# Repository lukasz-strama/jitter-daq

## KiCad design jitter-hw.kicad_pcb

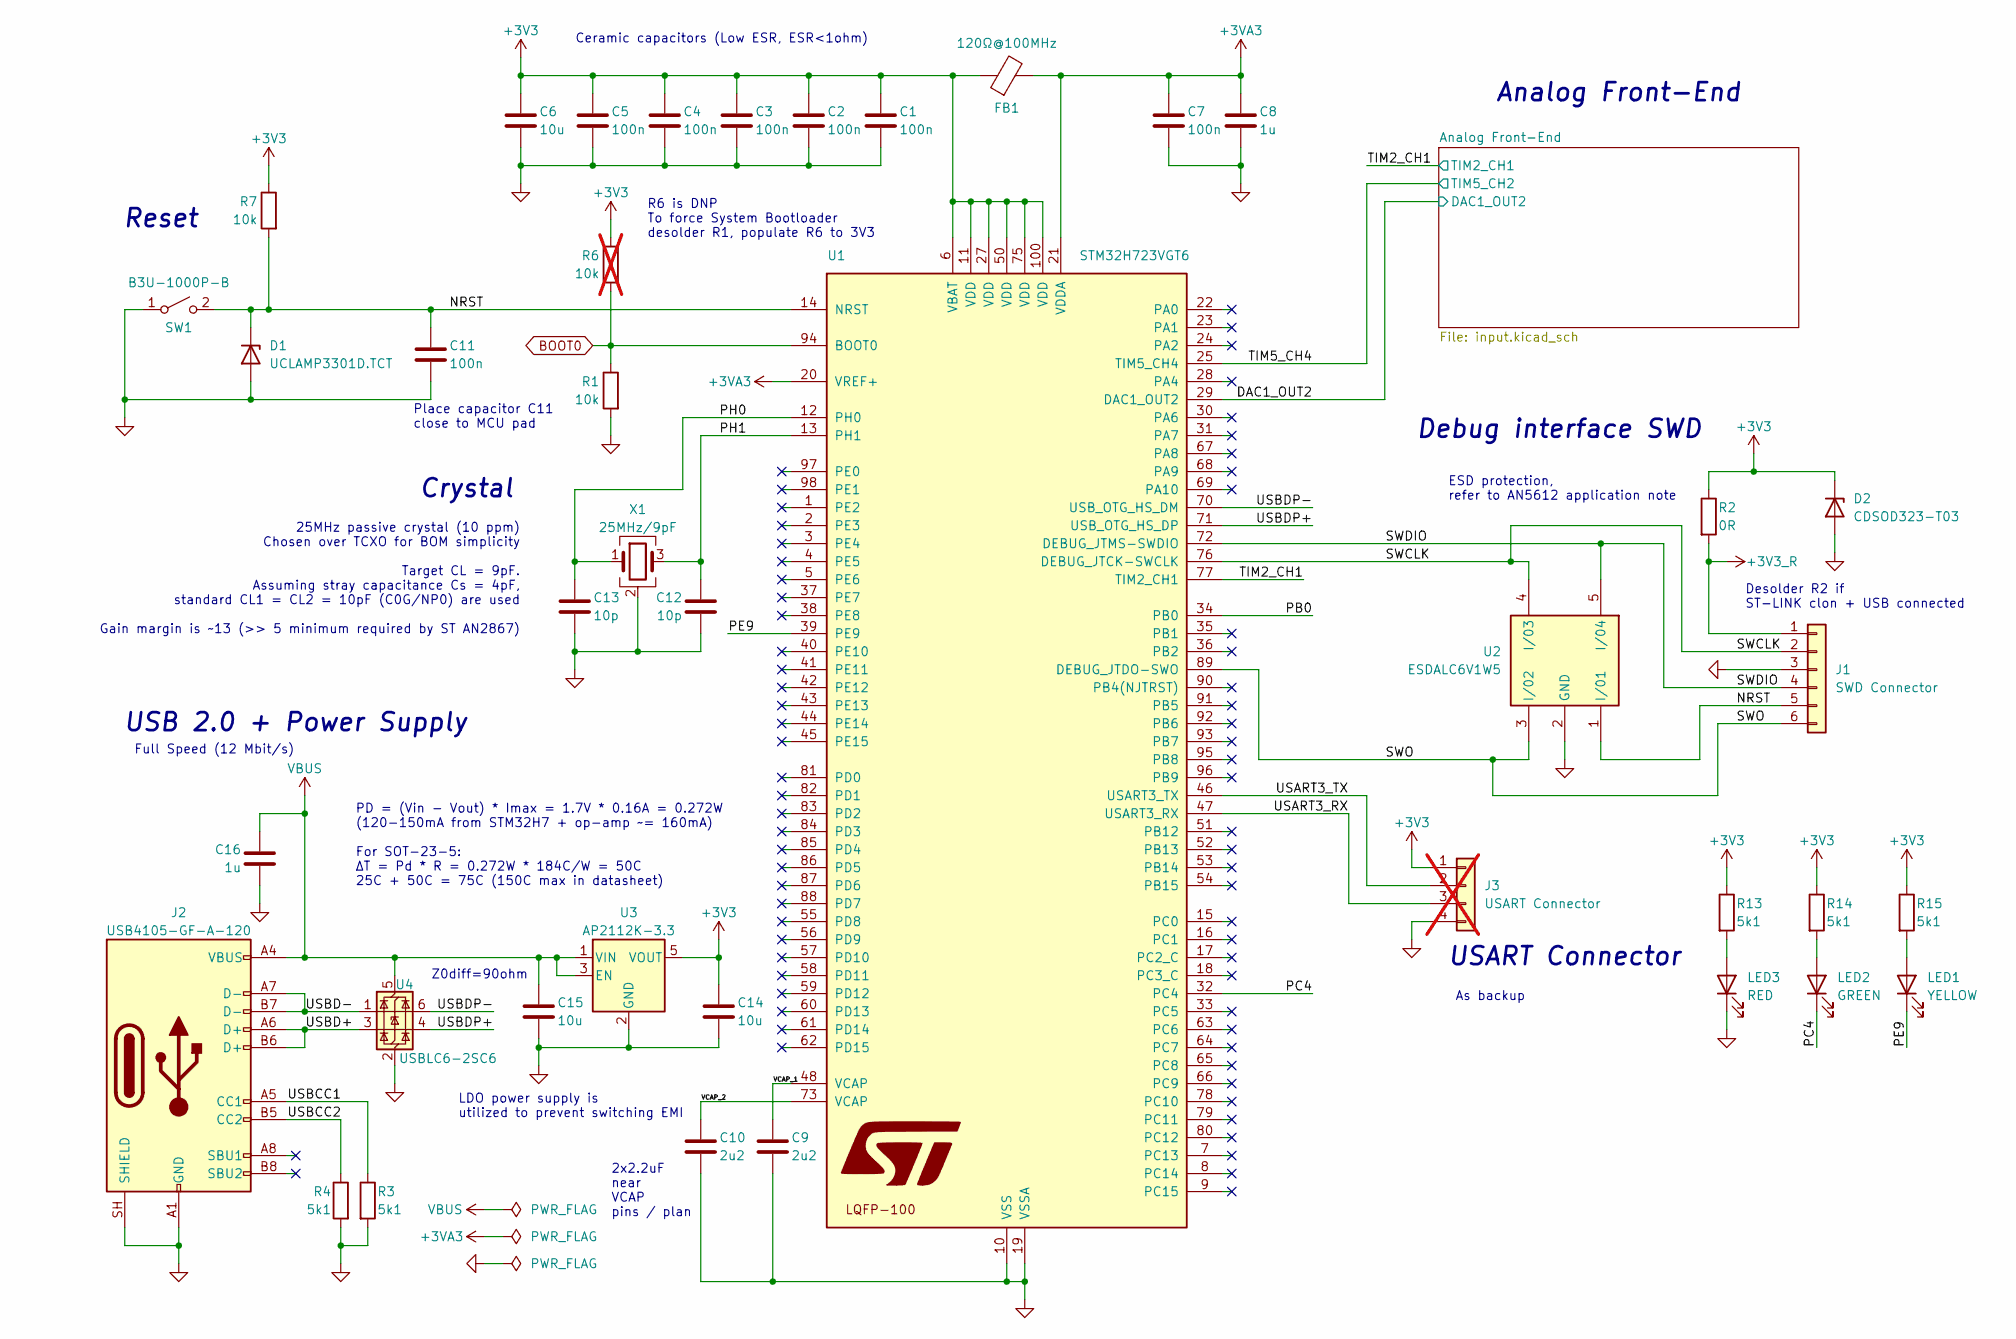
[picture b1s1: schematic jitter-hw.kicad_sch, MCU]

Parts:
C1, C2, C3, C4, C5, C7, C11: 100n; C_0603_1608Metric; Voltage 50V; Tolerance ±10%; MPN CL10B104KB8NNNC; DigiKey Part Number 1276-1000-1-ND
C6, C14, C15: 10u; C_0805_2012Metric; Voltage 25V; Tolerance ±10%; MPN CL21A106KAYNNNG; DigiKey Part Number 1276-6454-1-ND
C8, C16: 1u; C_0603_1608Metric; Voltage 25V; Tolerance ±10%; MPN CL10A105KA8NNNC; DigiKey Part Number 1276-1102-1-ND
C9, C10: 2u2; C_0603_1608Metric; Voltage 10V; Tolerance ±10%; MPN CL10B225KP8NNNC; DigiKey Part Number 1276-1134-1-ND
C12, C13: 10p; C_0603_1608Metric; Voltage 50V; Tolerance ±5%; MPN CL10C100JB8NNNC; DigiKey Part Number 1276-1027-1-ND
D1: UCLAMP3301D.TCT; D_SOD-323_HandSoldering; Voltage - Breakdown 3.5V; Voltage - Clamping 9.5V; MPN UCLAMP3301D.TCT; DigiKey Part Number UCLAMP3301DCT-ND
D2: CDSOD323-T03; D_SOD-323_HandSoldering; MPN CDSOD323-T03
FB1: 120Ω@100MHz; L_0603_1608Metric; Current Rating 2A; MPN BLM18PG121SN1D; DigiKey Part Number 490-1037-1-ND
J1: SWD Connector; PinHeader_1x06_P2.54mm_Vertical
J2: USB4105-GF-A-120; USB_C_Receptacle_GCT_USB4105-xx-A_16P_TopMnt_Horizontal; Voltage - Rated 48VDC; MPN USB4105-GF-A-120; DigiKey Part Number 2073-USB4105-GF-A-120CT-ND
J3: USART Connector; PinHeader_1x04_P2.54mm_Vertical; not fitted
LED1: YELLOW; LED_0805_2012Metric_Pad1.15x1.40mm_HandSolder; MPN KP-2012SYC
LED2: GREEN; LED_0805_2012Metric_Pad1.15x1.40mm_HandSolder; MPN KP-2012SGC
LED3: RED; LED_0805_2012Metric_Pad1.15x1.40mm_HandSolder; MPN KP-2012SURCK
R1, R7: 10k; R_0805_2012Metric; Tolerance ±1%; MPN RC0805FR-0710K; DigiKey Part Number 311-10.0KCRCT-ND
R2: 0R; R_0805_2012Metric; Tolerance Jumper; MPN RC0805FR-070RL; DigiKey Part Number 311-0.0CRCT-ND
R3, R4, R13, R14, R15: 5k1; R_0805_2012Metric; Tolerance ±1%; MPN RC0805FR-075K1; DigiKey Part Number 311-5.10KCRCT-ND
R6: 10k; R_0805_2012Metric; Tolerance ±1%; MPN RC0805FR-0710K; DigiKey Part Number 311-10.0KCRCT-ND; not fitted
SW1: B3U-1000P-B; SW_SPST_B3U-1000P; Contact Rating @ Voltage 0.05A @ 12VDC; MPN B3U-1000P-B; DigiKey Part Number SW1143CT-ND
U1: STM32H723VGT6; LQFP-100_14x14mm_P0.5mm; Voltage 1.71V ~ 3.6V; MPN STM32H723VGT6; DigiKey Part Number 497-STM32H723VGT6TRCT-ND
U2: ESDALC6V1W5; SOT65P210X110-5N; Voltage - Reverse Stand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 3V; Voltage - Clamping 9.5V; MPN ESDALC6V1W5; DigiKey Part Number 497-7231-1-ND
U3: AP2112K-3.3; SOT-23-5; Voltage - Input 6V; Voltage - Output 3.3V; MPN AP2112K-3.3TRG1; DigiKey Part Number AP2112K-3.3TRG1DICT-ND
U4: USBLC6-2SC6; SOT-23-6; Voltage - Reverse Stand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 5.25V; Voltage - Breakdown 6V; MPN USBLC6-2SC6; DigiKey Part Number 497-11882-1-ND
X1: 25MHz/9pF; Crystal_SMD_3225-4Pin_3.2x2.5mm; MPN 3225-25M-SR

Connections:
+3V3: C1.1, C2.1, C3.1, C4.1, C5.1, C6.1, C14.1, D2.1 (K), FB1.1, J3.1, R2.1, R6.1, R7.1, R13.1, R14.1, R15.1, U1.6 (VBAT), U1.11 (VDD), U1.27 (VDD), U1.50 (VDD), U1.75 (VDD), U1.100 (VDD), U3.5 (VOUT)
+3V3_R: J1.1, R2.2
+3VA3: C7.1, C8.1, FB1.2, U1.20 (VREF+), U1.21 (VDDA); also elsewhere on the board
/DAC1_OUT2: U1.29 (DAC1_OUT2); also elsewhere on the board
/NRST: C11.1, D1.1 (K), J1.5, R7.2, SW1.2 (B), U1.14 (NRST), U2.1 (I/01)
/PB0: U1.34 (PB0)
/PC4: LED2.1 (K), U1.32 (PC4)
/PE9: LED1.1 (K), U1.39 (PE9)
/PH0: C13.1, U1.12 (PH0), X1.1
/PH1: C12.1, U1.13 (PH1), X1.3
/SWCLK: J1.2, U1.76 (DEBUG_JTCK-SWCLK), U2.4 (I/03)
/SWDIO: J1.4, U1.72 (DEBUG_JTMS-SWDIO), U2.5 (I/04)
/SWO: J1.6, U1.89 (DEBUG_JTDO-SWO), U2.3 (I/02)
/TIM2_CH1: U1.77 (TIM2_CH1); also elsewhere on the board
/TIM5_CH4: U1.25 (TIM5_CH4); also elsewhere on the board
/USART3_RX: J3.3, U1.47 (USART3_RX)
/USART3_TX: J3.2, U1.46 (USART3_TX)
/USBCC1: J2.A5 (CC1), R3.1
/USBCC2: J2.B5 (CC2), R4.1
/USBD+: J2.A6 (D+), J2.B6 (D+), U4.3 (I/O2)
/USBD-: J2.A7 (D-), J2.B7 (D-), U4.1 (I/O1)
/USBDP+: U1.71 (USB_OTG_HS_DP), U4.4 (I/O2)
/USBDP-: U1.70 (USB_OTG_HS_DM), U4.6 (I/O1)
/VCAP_1: C9.1, U1.48 (VCAP)
/VCAP_2: C10.1, U1.73 (VCAP)
BOOT0: R1.1, R6.2, U1.94 (BOOT0)
GND: C1.2, C2.2, C3.2, C4.2, C5.2, C6.2, C7.2, C8.2, C9.2, C10.2, C11.2, C12.2, C13.2, C14.2, C15.2, C16.2, D1.2 (A), D2.2 (A), J1.3, J2.A1 (GND), J2.A12 (GND), J2.B1 (GND), J2.B12 (GND), J2.SH (SHIELD), J3.4, LED3.1 (K), R1.2, R3.2, R4.2, SW1.1 (A), U1.10 (VSS), U1.19 (VSSA), U1.26 (VSS), U1.49 (VSS), U1.74 (VSS), U1.99 (VSS), U2.2 (GND), U3.2 (GND), U4.2 (GND), X1.2 (G), X1.4 (G); also elsewhere on the board
unnamed: LED1.2 (A), R15.2
unnamed: LED2.2 (A), R14.2
unnamed: LED3.2 (A), R13.2
VBUS: C15.1, C16.1, J2.A4 (VBUS), J2.A9 (VBUS), J2.B4 (VBUS), J2.B9 (VBUS), U3.1 (VIN), U3.3 (EN), U4.5 (VBUS)

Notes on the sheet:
R6 is DNP To force System Bootloader desolder R1, populate R6 to 3V3
ESD protection, refer to AN5612 application note
USART Connector
As backup
Desolder R2 if ST-LINK clon + USB connected
Place capacitor C11 close to MCU pad
2x2.2uF near VCAP pins / plan
PD = (Vin - Vout) * Imax = 1.7V * 0.16A = 0.272W (120-150mA from STM32H7 + op-amp ~= 160mA) For SOT-23-5: ΔT = Pd * R = 0.272W * 184C/W = 50C 25C + 50C = 75C (150C max in datasheet)
Ceramic capacitors (Low ESR, ESR<1ohm)
LDO power supply is utilized to prevent switching EMI
USB 2.0 + Power Supply
Full Speed (12 Mbit/s)
Z0diff=90ohm
Crystal
Reset
Debug interface SWD
25MHz passive crystal (10 ppm) Chosen over TCXO for BOM simplicity Target CL = 9pF. Assuming stray capacitance Cs = 4pF, standard CL1 = CL2 = 10pF (C0G/NP0) are used Gain margin is ~13 (>> 5 minimum required by ST AN2867)
Analog Front-End

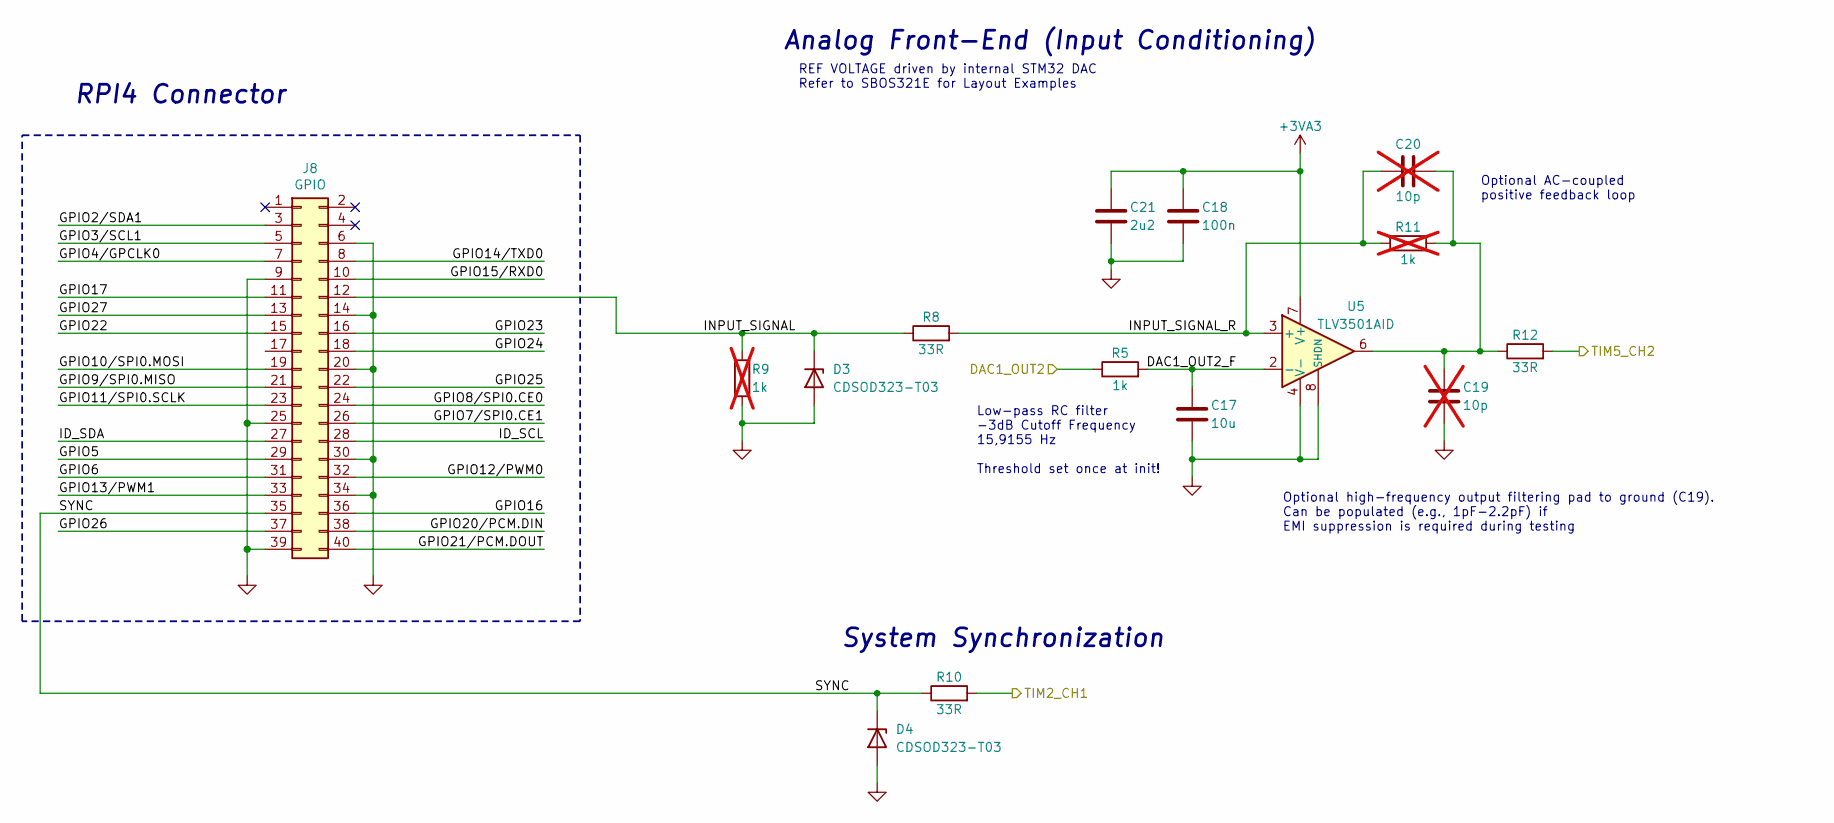
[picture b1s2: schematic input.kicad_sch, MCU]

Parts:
C17: 10u; C_0805_2012Metric; Voltage 25V; Tolerance ±10%; MPN CL21A106KAYNNNG; DigiKey Part Number 1276-6454-1-ND
C18: 100n; C_0603_1608Metric; Voltage 50V; Tolerance ±10%; MPN CL10B104KB8NNNC; DigiKey Part Number 1276-1000-1-ND
C19, C20: 10p; C_0603_1608Metric; Voltage 50V; Tolerance ±5%; MPN CL10C100JB8NNNC; DigiKey Part Number 1276-1027-1-ND; not fitted
C21: 2u2; C_0603_1608Metric; Voltage 10V; Tolerance ±10%; MPN CL10B225KP8NNNC; DigiKey Part Number 1276-1134-1-ND
D3, D4: CDSOD323-T03; D_SOD-323_HandSoldering; MPN CDSOD323-T03
J8: GPIO; PinSocket_2x20_P2.54mm_Vertical
R5: 1k; R_0805_2012Metric; Tolerance ±1%; MPN RC0805FR-071K; DigiKey Part Number YAG1321CT-ND
R8, R10, R12: 33R; R_0805_2012Metric; Tolerance ±1%; MPN RC0805FR-0733RL; DigiKey Part Number 311-33.0CRCT-ND
R9, R11: 1k; R_0805_2012Metric; Tolerance ±1%; MPN RC0805FR-071K; DigiKey Part Number YAG1321CT-ND; not fitted
U5: TLV3501AID; SOIC-8_3.9x4.9mm_P1.27mm; Voltage - Input Offset 6.5mV @ 5.5V; MPN TLV3501AID; DigiKey Part Number 296-17921-5-ND

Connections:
+3VA3: C18.1, C21.1, U5.7 (V+); also elsewhere on the board
/Analog Front-End/DAC1_OUT2_F: C17.1, R5.2, U5.2 (-)
/Analog Front-End/GPIO2/SDA1: J8.3
/Analog Front-End/GPIO3/SCL1: J8.5
/Analog Front-End/GPIO4/GPCLK0: J8.7
/Analog Front-End/GPIO5: J8.29
/Analog Front-End/GPIO6: J8.31
/Analog Front-End/GPIO7/SPI0.CE1: J8.26
/Analog Front-End/GPIO8/SPI0.CE0: J8.24
/Analog Front-End/GPIO9/SPI0.MISO: J8.21
/Analog Front-End/GPIO10/SPI0.MOSI: J8.19
/Analog Front-End/GPIO11/SPI0.SCLK: J8.23
/Analog Front-End/GPIO12/PWM0: J8.32
/Analog Front-End/GPIO13/PWM1: J8.33
/Analog Front-End/GPIO14/TXD0: J8.8
/Analog Front-End/GPIO15/RXD0: J8.10
/Analog Front-End/GPIO16: J8.36
/Analog Front-End/GPIO17: J8.11
/Analog Front-End/GPIO20/PCM.DIN: J8.38
/Analog Front-End/GPIO21/PCM.DOUT: J8.40
/Analog Front-End/GPIO22: J8.15
/Analog Front-End/GPIO23: J8.16
/Analog Front-End/GPIO24: J8.18
/Analog Front-End/GPIO25: J8.22
/Analog Front-End/GPIO26: J8.37
/Analog Front-End/GPIO27: J8.13
/Analog Front-End/ID_SCL: J8.28
/Analog Front-End/ID_SDA: J8.27
/Analog Front-End/INPUT_SIGNAL: D3.1 (K), J8.12, R8.1, R9.1
/Analog Front-End/INPUT_SIGNAL_R: C20.1, R8.2, R11.1, U5.3 (+)
/Analog Front-End/SYNC: D4.1 (K), J8.35, R10.1
/DAC1_OUT2: R5.1; also elsewhere on the board
/TIM2_CH1: R10.2; also elsewhere on the board
/TIM5_CH4: R12.2; also elsewhere on the board
GND: C17.2, C18.2, C19.2, C21.2, D3.2 (A), D4.2 (A), J8.6, J8.9, J8.14, J8.20, J8.25, J8.30, J8.34, J8.39, R9.2, U5.4 (V-), U5.8 (SHDN); also elsewhere on the board
unnamed: C19.1, C20.2, R11.2, R12.1, U5.6

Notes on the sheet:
REF VOLTAGE driven by internal STM32 DAC Refer to SBOS321E for Layout Examples
Optional high-frequency output filtering pad to ground (C19). Can be populated (e.g., 1pF-2.2pF) if EMI suppression is required during testing
System Synchronization
RPI4 Connector
Low-pass RC filter -3dB Cutoff Frequency 15,9155 Hz Threshold set once at init!
Analog Front-End (Input Conditioning)
Optional AC-coupled positive feedback loop

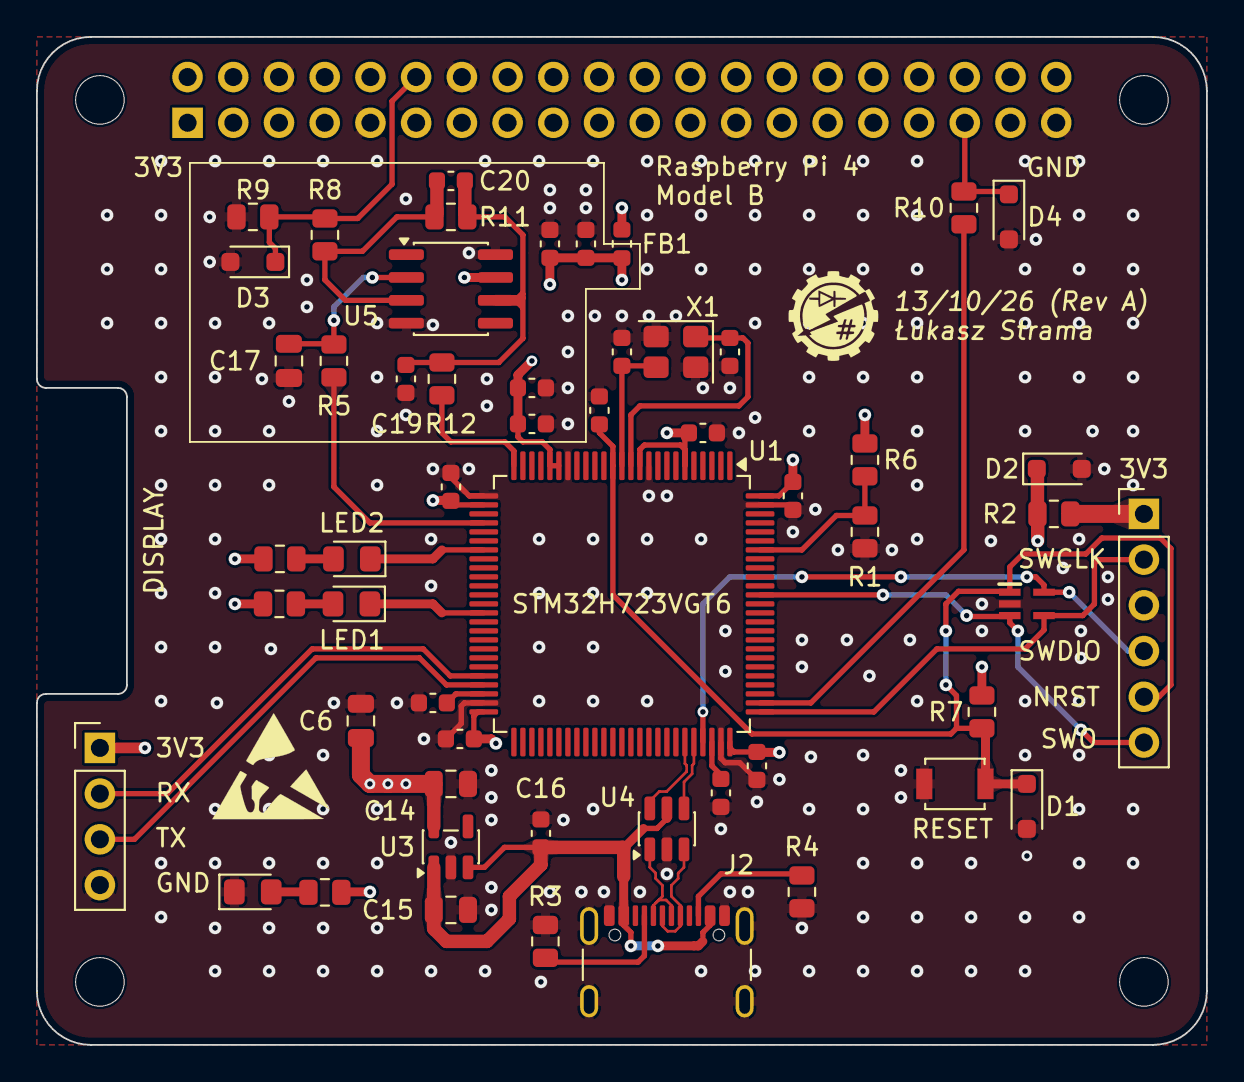
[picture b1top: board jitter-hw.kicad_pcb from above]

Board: 4 copper layers, 65.0 x 56.0 mm, 59 parts (1 on the bottom side), 35 nets.

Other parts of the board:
MH1, MH2, MH3, MH4: MountingHole_2.7mm_M2.5
